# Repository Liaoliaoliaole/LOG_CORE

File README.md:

<div align="center">  </div>

# Morfeas-Core
This repository related to Morfeas core where is a sub-project of the Morfeas Project.

### The name "Morfeas"
Morfeas is the Latinisation of the Greek word "Μορφέας" which translate as:
Him that can give or change form (or shape). The name "Morfeas" describe the design [Philosophy](#design-philosophy)
of the project. Many small building blocks that change the form of the information from one protocol to other(s).

### Project Description
The Morfeas project was initially start as an implementation of a software gateway solution system
(currently named Morfeas-Proto) that provide (and translate) measurements data from some proprietary devices (SDAQ family)
with CANbus compatible interface (SDAQnet) to OPC-UA protocol (Open62541 based).

As the Morfeas project developed additional support added for other devices (MDAQ, IO-BOX, MTI, UniNOx) with different interfaces (ModBus-TCP, USB).

Furthermore, a web interface sub-project added to the Morfeas project under the name ["Morfeas-web"](https://gitlab.com/fantomsam/morfeas_web).
Thisof, will provide a layman friendly configuration interface for the gateway, the OPC-UA server's Nodeset and the connected devices.

**In relation with this project [Morfeas_RPi_Hat](./src/Morfeas_RPi_Hat)**
### Design Philosophy
The Morfeas-core project designed as a micro-component with supervision system.
This means that all the components called from a supervisor programs,
runs as daemon type processes, and they communicating using messages established from the **Morfeas IPC protocol**
that passing through **PIPEs**. All the project's components are written in **ANSI C**.

### Documentation
Project documentation located @:[/Docs/Morfeas_project_Documentation](./Docs/Morfeas_project_Documentation)

#### The Morfeas-core components:
* **Morfeas_daemon**: The supervisor.
* **Morfeas_opc_ua**: OPC-UA server.
* Driver/Handler for each supported interface:
  * **Morfeas_SDAQ_if**: SDAQ_net handler.
  * **Morfeas_MDAQ_if**: ModBus-TCP handler for MDAQs.
  * **Morfeas_IOBOX_if**: ModBus-TCP handler for IO-BOXes.
  * **Morfeas_MTI_if**: ModBus-TCP handler for MTIs.
  * **Morfeas_NOX_if**: CANBus handler for UniNOx.

### Requirements
For compilation of this project the following dependencies required.
* [GCC](https://gcc.gnu.org/) - The GNU Compilers Collection.
* [GNU Make](https://www.gnu.org/software/make/) - GNU make utility.
* [CMake](https://cmake.org/) - Cross-platform family of open source tools for package build.
* [OpenSSL](https://www.openssl.org/) - A full-featured toolkit for TLS and SSL protocols.
* [GnuTLS](https://gnutls.org/) - A secure communications library for SSL, TLS and DTLS protocols.
* [zlib](https://www.zlib.net/zlib_how.html) - A free software library used for data compression.
* [NCURSES](https://www.gnu.org/software/ncurses/ncurses.html) - A free (libre) software emulation library of curses.
* [GLib](https://wiki.gnome.org/Projects/GLib) - GNOME core application building blocks libraries.
* [LibGTop](https://developer.gnome.org/libgtop/stable/) - A library to get system specific data.
* [libxml2](http://xmlsoft.org/) - Library for parsing XML documents.
* [libmodbus](https://www.libmodbus.org/) - A free software library for communication via ModBus protocol.
* [Libsocketcan](https://directory.fsf.org/wiki/Libsocketcan) - Library to control some basic functions in SocketCAN from userspace.
* [libi2c](https://packages.debian.org/jessie/libi2c-dev) - A library that provide I2C functionality to Userspace.
* [libdbus](https://www.freedesktop.org/wiki/Software/dbus/#index1h1) - The library of the D-Bus.
<!--* [Libwebsockets](https://libwebsockets.org/) - An ANSI C library for implementing modern network protocols.
	* [libusb](https://libusb.info/) - An ANSI C library that provides generic access to USB devices.-->

##### Optionally
* [CAN-Utils](https://elinux.org/Can-utils) - CANBus utilities.
* [I2C-tools](https://packages.debian.org/jessie/i2c-tools) - Heterogeneous set of I2C tools for Linux kernel.

## The Source
The source of the Morfeas-core project have the following submodules:
* [SDAQ_worker](https://gitlab.com/fantomsam/sdaq-worker) - A libre (free) utilities suite for SDAQ devices.
* [cJSON](https://github.com/DaveGamble/cJSON) - An Ultralightweight open source JSON parser for ANSI C.
* [noPoll](http://www.aspl.es/nopoll/) - An open source ANSI C implementation of WebSocket (RFC 6455).
* [open62541](https://open62541.org/) - An open source C (C99) implementation of OPC-UA (IEC 62541).

### Get the Source
```
$ # Clone the project's source code
$ git clone https://gitlab.com/fantomsam/morfeas_project.git Morfeas_core
$ cd Morfeas_core
$ # Get Source of the submodules
$ git submodule update --init --recursive --remote --merge
```
### Compilation and installation of the submodules

#### cJSON
```
$ cd src/cJSON
$ mkdir build && cd build
$ cmake -D BUILD_SHARED_LIBS=ON ..
$ make -j$(nproc)
$ sudo make install
$ sudo ldconfig
```
#### noPoll
```
$ cd src/noPoll
$ ./autogen.sh
$ make -j$(nproc)
$ sudo make install
$ sudo ldconfig
```
#### Open62541
```
$ cd src/open62541
$ mkdir build && cd build
$ cmake -D BUILD_SHARED_LIBS=ON ..
$ make -j$(nproc)
$ sudo make install
$ sudo ldconfig
```
#### SDAQ_worker
```
$ cd src/sdaq_worker
$ make tree
$ make -j$(nproc)
$ sudo make install
```
### Compilation of the Morfeas-core Project
```
$ make tree
$ make -j$(nproc)
```
The executable binaries located under the **./build** directory.

### Installation of the Morfeas-core Project
```
$ sudo make install
```
### Configuration for the Morfeas_daemon, D-Bus and Systemd service
```
$ #--- Optionaly copy the configuration directory to your home ---
$ cp -r configuration ~/
$ #Make the nececery modifications on the Morfeas_daemon configuration (.xml) file
$ vim (~/)configuration/Morfeas_config.xml
$ #Make the nececery modifications on the Unit file of the Morfeas_daemon service
$ sudo systemctl edit Morfeas_system.service --full
$ #Also modify the configuration file of the Morfeas_daemon service
$ sudo vim /etc/systemd/system/Morfeas_system.service.d/Morfeas_system.conf
$ #Modify the D-Bus configuration for the Morfeas system
$ sudo vim /etc/dbus-1/system.d/Morfeas_system.conf
$ #Start the systemd service daemon
$ sudo systemctl start Morfeas_system.service
$ #--- Optionaly If you want to start the daemon on boot ---
$ sudo systemctl enable Morfeas_system.service
```
### Re-Compilation of the source
Guide link [here](./RE-INSTALL.md)

## Authors
* **Sam Harry Tzavaras** - *Initial work*

## License
The source code of the project is licensed under GPLv3 or later - see the [License](LICENSE) file for details.

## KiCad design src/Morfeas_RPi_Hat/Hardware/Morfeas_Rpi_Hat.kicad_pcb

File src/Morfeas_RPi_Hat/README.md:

<div align="center">  </div>

# Morfeas PRi Hat
This repository related to Supporting software, PCB and Mechanical design for the Morfeas RPi Hat.

The PCB designed using [KiCAD EDA](https://kicad-pcb.org/), A Libre(free) Electronic CAD/CAM software.<br>
The mechanical design of the enclosures designed using [FreeCAD](https://www.freecadweb.org/), A Libre(free) Mechanical/Architecture CAD/CAM Software.<br>
The software for the Morfeas RPi Hat written in ANSI C and is compatible with GNU operating system.<br>

### Requirements
For compilation of this project the following dependencies are required.
* [GCC](https://gcc.gnu.org/) - The GNU Compilers Collection
* [GNU Make](https://www.gnu.org/software/make/) - GNU make utility
* [NCURSES](https://www.gnu.org/software/ncurses/ncurses.html) - A free (libre) software emulation library of curses.
* [GLib](https://wiki.gnome.org/Projects/GLib) - GNOME core application building blocks libraries.
* [LibGTop](https://developer.gnome.org/libgtop/stable/) - A library to get system specific data.
* [libi2c](https://packages.debian.org/jessie/libi2c-dev) - A library that provide I2C functionality to Userspace
* [libmodbus](https://www.libmodbus.org/) - A free software library for communication via ModBus protocol.

##### Optionally
* [I2C-tools](https://packages.debian.org/jessie/i2c-tools) - Heterogeneous set of I2C tools for Linux kernel

### Compilation
To compile the program (tested under GNU/Linux only)
```
$ # Make the compilation directory tree
$ make tree
$ make
```
The executable binary located under the **./build** directory.

### Installation
```
$ sudo make install
```
### Un-installation
```
$ sudo make uninstall
```
### Usage: Morfeas_RPi_Hat
```
Usage: Morfeas_RPi_Hat [Options]

	Options:
	         -h : Print Help
	         -v : Print Version
	         -b : I2C Bus number (default 1)

		-----Morfeas_RPi_Hat Shell-----
KEYS:
 	KEY_UP    = Buffer up
	KEY_DOWN  = Buffer Down
	KEY_LEFT  = Cursor move left by 1
	KEY_RIGTH = Cursor move Right by 1
	Ctrl + C  = Clear current buffer
	Ctrl + L  = Clear screen
	Ctrl + I  = print used CAN-if
	Ctrl + Q  = Quit
COMMANDS:
	meas p# = Print measurement of Port's CSA
	config p# = Print Port's Configuration
	set p# czero = Set port's current zero offset
	set p# vzero = Set port's voltage zero offset
	set p# vgain Ref_value = Calculate and set CSA's voltage gain at Reference value
	set p# cgain Ref_value = Calculate and set CSA's current gain at Reference value
	save p# = Save Port's configuration to EEPROM
```

## Documentation
The documentation is located under the [Docs](./Docs) directory.

## Authors
* **Sam Harry Tzavaras** - *Initial work*
## License
The PCB design is licensed under TAPRv1 or later - see the [License](./Hardware/TAPR_Open_Hardware_License_v1.0.pdf) file for details.

The Source code is licensed under GPLv3 or later - see the [License](../blob/master/LICENSE) file for details.

The Technical Reference is licensed under FDLv1.3 or later - see the [License](../../fdl-1.3.md) file for details.

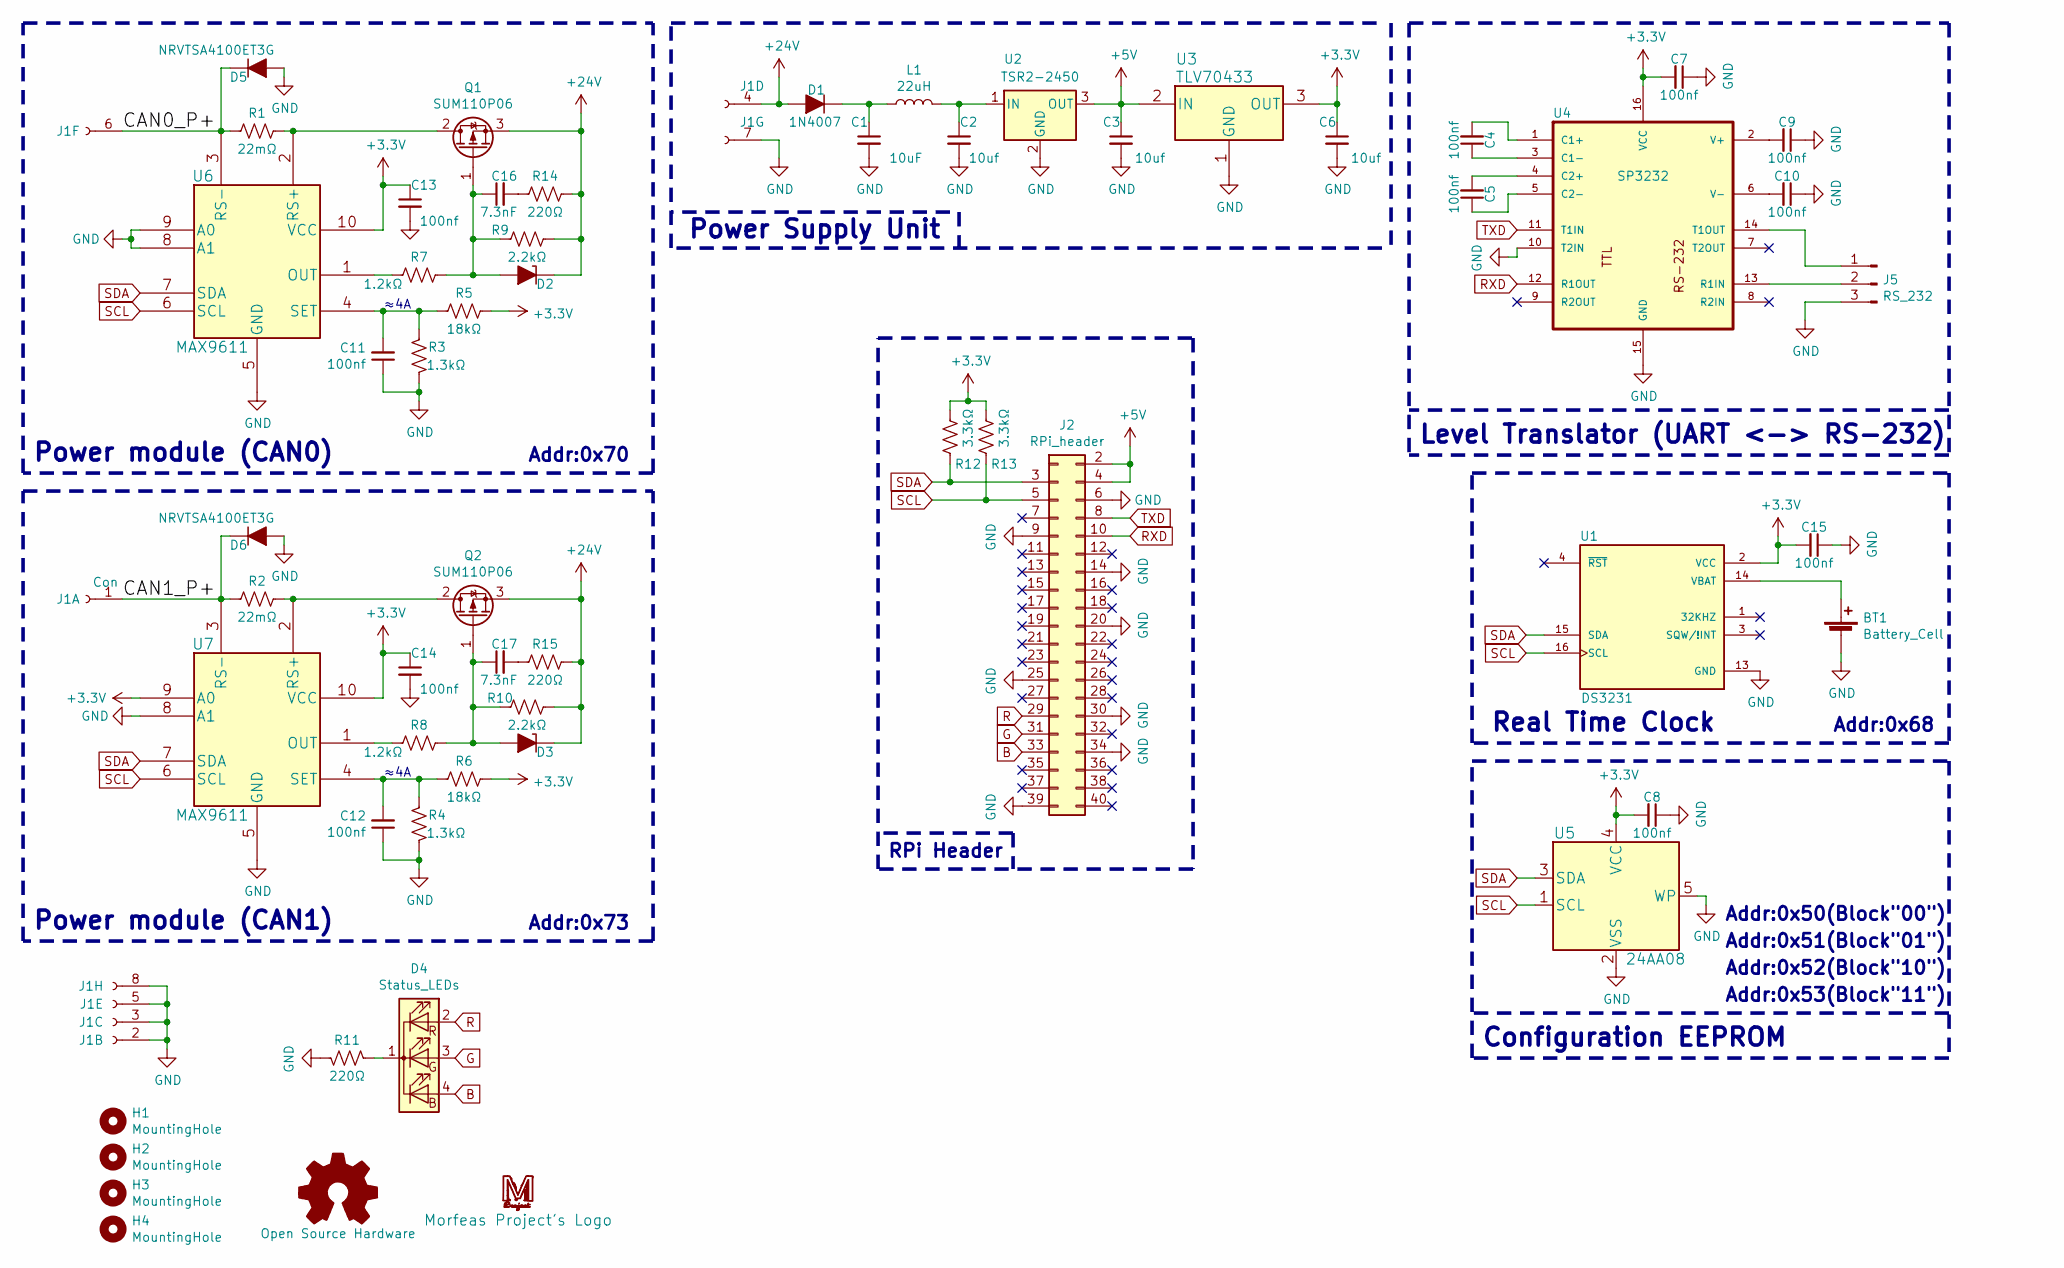
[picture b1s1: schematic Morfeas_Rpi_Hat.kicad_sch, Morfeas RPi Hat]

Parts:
BT1: Battery_Cell; CH252032LF
C1: 10uF; C_1210_3225Metric
C2, C3, C6: 10uf; C_1210_3225Metric
C4, C5, C7, C8, C9, C10, C11, C12, C13, C14, C15: 100nf; C_0805_2012Metric
C16, C17: 7.3nF; C_0805_2012Metric
D1: 1N4007; DO-214AC(SMA)
D2, D3: Zener10V; D_DO-35_SOD27_P7.62mm_Horizontal
D4: Status_LEDs; PinSocket_1x04_P2.54mm_Vertical
D5, D6: NRVTSA4100ET3G; DO-214AC(SMA)
H1, H2, H3, H4: MountingHole; MountingHole_3.5mm
J1: Con; SPT1.5_8-H-3.5
J2: RPi_header; PinSocket_2x20_P2.54mm_Vertical
J5: RS_232; PinSocket_1x03_P2.54mm_Vertical
L1: 22uH; INDPM6060X300N
Morfeas_project_Logo1: Morfeas Project's Logo; Morfeas_logo_big_silkscreen
Open_Source_hardware1: Open Source Hardware; OSHW-Logo2_9.8x8mm_SilkScreen
Q1, Q2: SUM110P06; TO-263-2
R1, R2: 22mΩ; R_2512_6332Metric
R3, R4: 1.3kΩ; R_1206_3216Metric
R5, R6: 18kΩ; R_1206_3216Metric
R7, R8: 1.2kΩ; R_1206_3216Metric
R9, R10: 2.2kΩ; R_1206_3216Metric
R11, R14, R15: 220Ω; R_1206_3216Metric
R12, R13: 3.3kΩ; R_1206_3216Metric
U1: DS3231; SOIC127P1032X265-16N
U2: TSR2-2450
U3: TLV70433; TLV70433DBVT
U4: SP3232; SOIC-16_3.9x9.9mm_P1.27mm
U5: 24AA08; 24AA08T-I&slash_OT
U6, U7: MAX9611; MAX9611AUB&plus_

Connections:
+3V3: C6.1, C7.2, C8.2, C13.1, C14.1, C15.2, R5.2, R6.2, R12.1, R13.1, U1.2 (VCC), U3.3 (OUT), U4.16 (VCC), U5.4 (VCC), U6.10 (VCC), U7.9 (A0), U7.10 (VCC)
+5V: C3.1, J2.2, J2.4, U2.3 (OUT), U3.2 (IN)
+24V: D1.2 (A), D2.1 (K), D3.1 (K), J1.4, Q1.3 (S), Q2.3 (S), R9.2, R10.2, R14.2, R15.2
/CAN0_P+: D5.1 (K), J1.6, R1.2, U6.3 (RS-)
/CAN1_P+: D6.1 (K), J1.1, R2.2, U7.3 (RS-)
B: D4.4 (BA), J2.33
G: D4.3 (GA), J2.31
GND: BT1.2 (-), C1.2, C2.2, C3.2, C6.2, C7.1, C8.1, C9.1, C10.1, C11.1, C12.1, C13.2, C14.2, C15.1, D5.2 (A), D6.2 (A), J1.2, J1.3, J1.5, J1.7, J1.8, J2.6, J2.9, J2.14, J2.20, J2.25, J2.30, J2.34, J2.39, J5.3, R3.1, R4.1, R11.2, U1.13 (GND), U2.2 (GND), U3.1 (GND), U4.10 (T2IN), U4.15 (GND), U5.2 (VSS), U5.5 (WP), U6.5 (GND), U6.8 (A1), U6.9 (A0), U7.5 (GND), U7.8 (A1)
unnamed: BT1.1 (+), U1.14 (VBAT)
unnamed: C1.1, D1.1 (K), L1.1
unnamed: C2.1, L1.2, U2.1 (IN)
unnamed: C4.1, U4.3 (C1-)
unnamed: C4.2, U4.1 (C1+)
unnamed: C5.1, U4.5 (C2-)
unnamed: C5.2, U4.4 (C2+)
unnamed: C9.2, U4.2 (V+)
unnamed: C10.2, U4.6 (V-)
unnamed: C11.2, R3.2, R5.1, U6.4 (SET)
unnamed: C12.2, R4.2, R6.1, U7.4 (SET)
unnamed: C16.1, D2.2 (A), Q1.1 (G), R7.1, R9.1
unnamed: C16.2, R14.1
unnamed: C17.1, D3.2 (A), Q2.1 (G), R8.2, R10.1
unnamed: C17.2, R15.1
unnamed: D4.1 (K), R11.1
unnamed: J5.1, U4.14 (T1OUT)
unnamed: J5.2, U4.13 (R1IN)
unnamed: Q1.2 (D), R1.1, U6.2 (RS+)
unnamed: Q2.2 (D), R2.1, U7.2 (RS+)
unnamed: R7.2, U6.1 (OUT)
unnamed: R8.1, U7.1 (OUT)
R: D4.2 (RA), J2.29
RXD: J2.10, U4.12 (R1OUT)
SCL: J2.5, R13.2, U1.16 (SCL), U5.1 (SCL), U6.6 (SCL), U7.6 (SCL)
SDA: J2.3, R12.2, U1.15 (SDA), U5.3 (SDA), U6.7 (SDA), U7.7 (SDA)
TXD: J2.8, U4.11 (T1IN)

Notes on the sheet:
Addr:0x50(Block"00")
Addr:0x68
Power module (CAN0)
Addr:0x70
Addr:0x53(Block"11")
≈4A
Power Supply Unit
Level Translator (UART <-> RS-232)
Real Time Clock
Power module (CAN1)
Addr:0x51(Block"01")
Addr:0x52(Block"10")
RPi Header
Addr:0x73
Configuration EEPROM

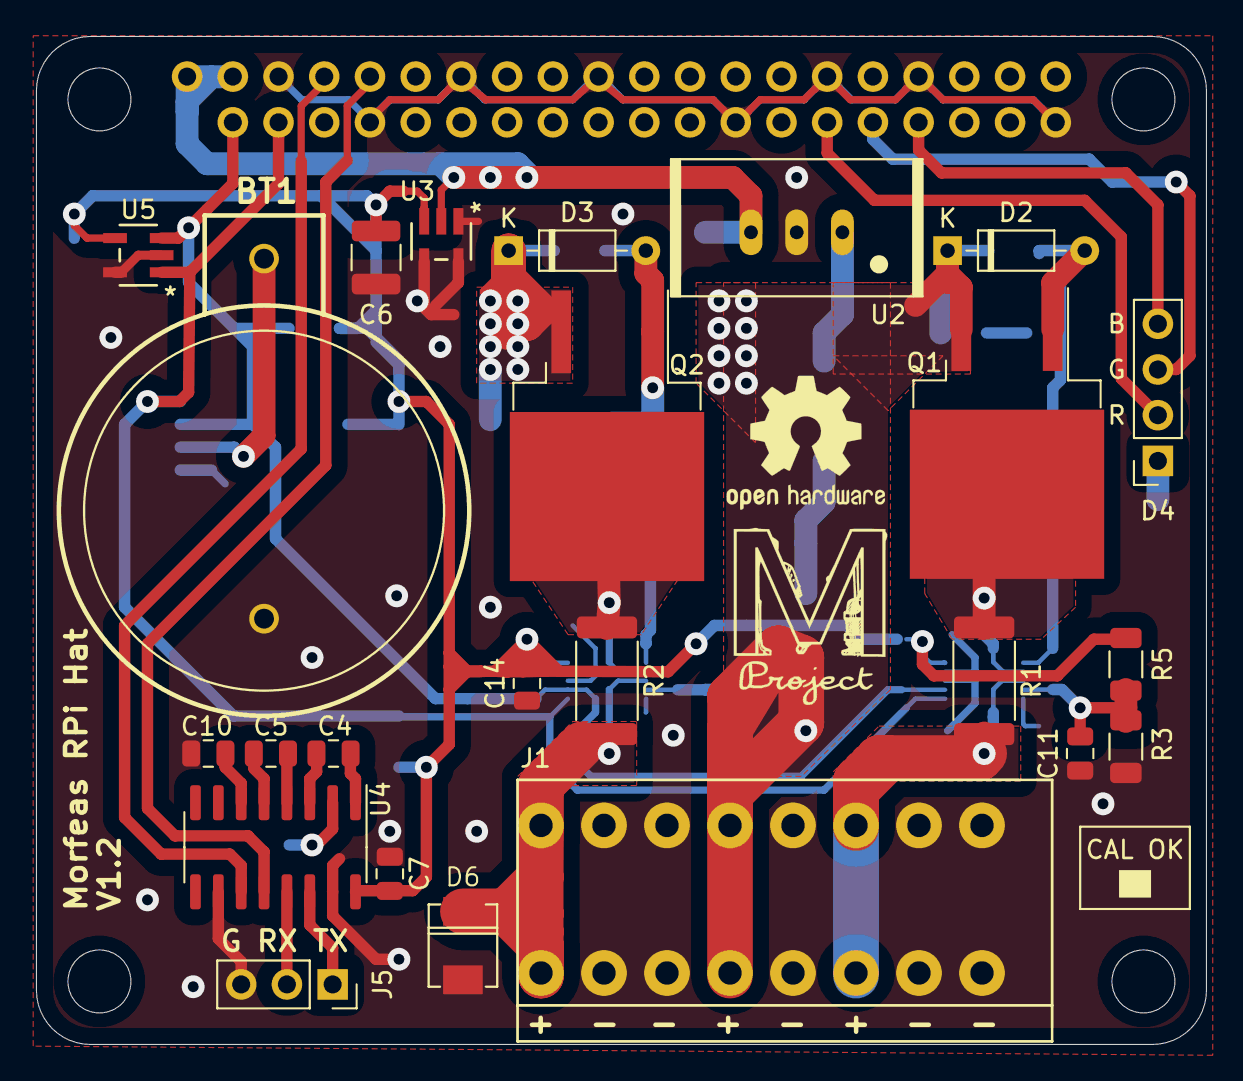
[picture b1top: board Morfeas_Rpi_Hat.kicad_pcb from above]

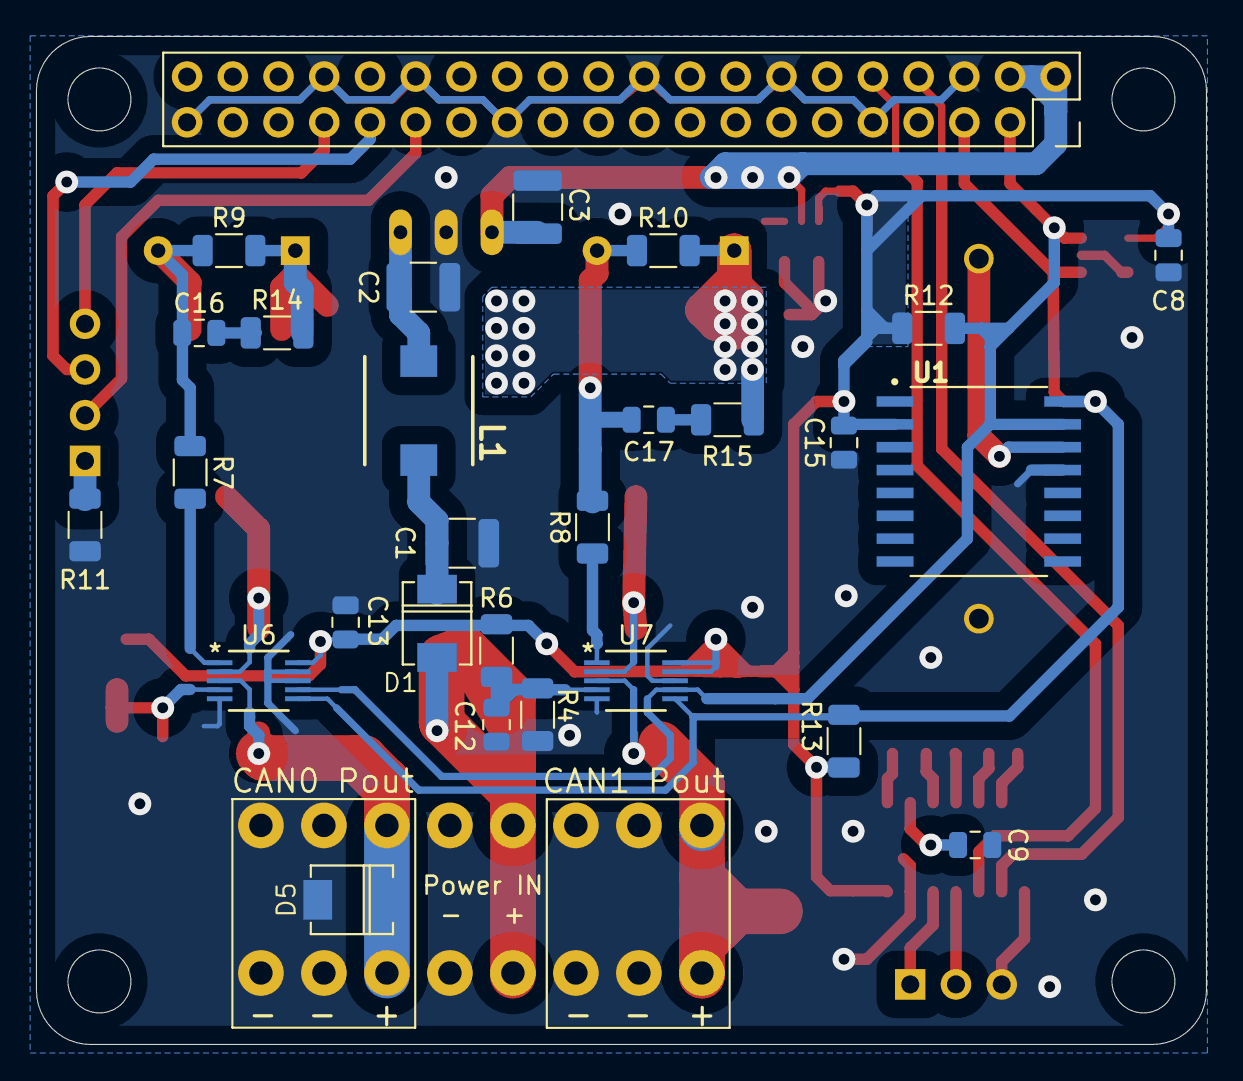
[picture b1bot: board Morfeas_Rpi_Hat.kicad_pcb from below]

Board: 2 copper layers, 65.0 x 56.0 mm, 58 parts (28 on the bottom side), 35 nets.

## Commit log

2025-02-24 Initialize Legacy code from original repo.
2025-02-24 Update git remove repo.
2025-02-28 update.
2025-02-28 change src/Morfeas_opc_ua/Morfeas_opc_ua_config.c back to UA_ServerConfig_clean to match with open62541 dependencies.

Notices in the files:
src/Morfeas_RPi_Hat/Hardware/Morfeas_Rpi_Hat.kicad_pcb:
Licence: TAPR Open Hardware License
